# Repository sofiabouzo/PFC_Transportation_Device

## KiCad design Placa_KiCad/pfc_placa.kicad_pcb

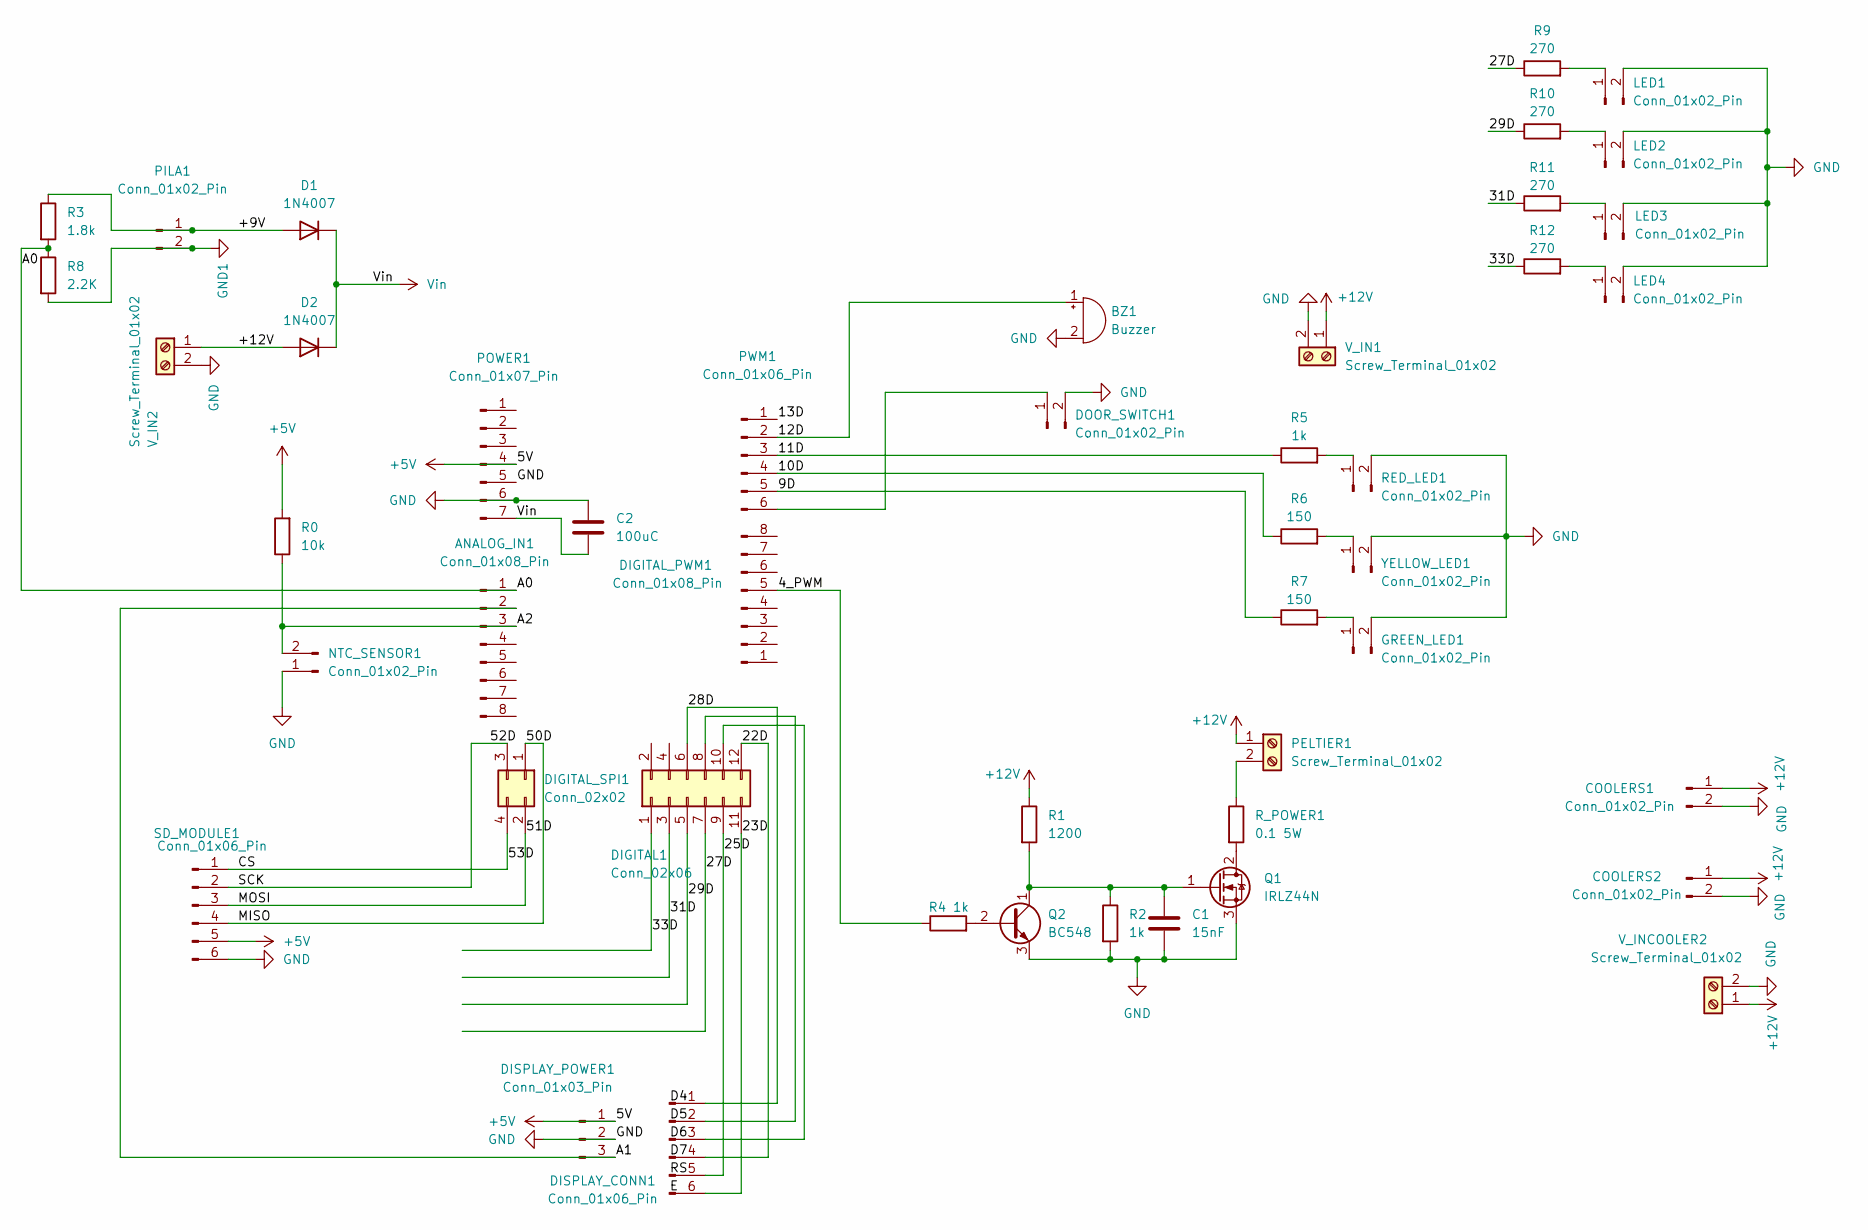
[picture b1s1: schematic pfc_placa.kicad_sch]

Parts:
ANALOG_IN1: Conn_01x08_Pin; PinHeader_1x08_P2.54mm_Vertical
BZ1: Buzzer; Buzzer_12x9.5RM7.6
C1: 15nF; C_Rect_L7.0mm_W2.5mm_P5.00mm
C2: 100uC; C_Radial_D5.0mm_H11.0mm_P2.00mm
COOLERS1, COOLERS2: Conn_01x02_Pin; JST_XH_B2B-XH-A_1x02_P2.50mm_Vertical
D1, D2: 1N4007; D_DO-41_SOD81_P10.16mm_Horizontal
DIGITAL1: Conn_02x06; PinHeader_2x06_P2.54mm_Vertical
DIGITAL_PWM1: Conn_01x08_Pin; PinHeader_1x08_P2.54mm_Vertical
DIGITAL_SPI1: Conn_02x02; PinHeader_2x02_P2.54mm_Vertical
DISPLAY_CONN1: Conn_01x06_Pin; PinHeader_1x06_P2.54mm_Vertical
DISPLAY_POWER1: Conn_01x03_Pin; PinHeader_1x03_P2.54mm_Vertical
DOOR_SWITCH1: Conn_01x02_Pin; PinHeader_1x02_P2.54mm_Vertical
GREEN_LED1: Conn_01x02_Pin; PinHeader_1x02_P2.54mm_Vertical
LED1, LED2, LED3, LED4: Conn_01x02_Pin; PinHeader_1x02_P2.54mm_Vertical
NTC_SENSOR1: Conn_01x02_Pin; JST_XH_B2B-XH-A_1x02_P2.50mm_Vertical
PELTIER1: Screw_Terminal_01x02; TerminalBlock_bornier-2_P5.08mm
PILA1: Conn_01x02_Pin; PinHeader_1x02_P2.54mm_Vertical
POWER1: Conn_01x07_Pin; PinHeader_1x07_P2.54mm_Vertical
PWM1: Conn_01x06_Pin; PinHeader_1x06_P2.54mm_Vertical
Q1: IRLZ44N; TO-220-3_Vertical
Q2: BC548; TO-92_Inline
R0: 10k; R_Axial_DIN0207_L6.3mm_D2.5mm_P7.62mm_Horizontal
R1: 1200; R_Axial_DIN0207_L6.3mm_D2.5mm_P7.62mm_Horizontal
R2, R4, R5: 1k; R_Axial_DIN0207_L6.3mm_D2.5mm_P7.62mm_Horizontal
R3: 1.8k; R_Axial_DIN0207_L6.3mm_D2.5mm_P7.62mm_Horizontal
R6, R7: 150; R_Axial_DIN0207_L6.3mm_D2.5mm_P7.62mm_Horizontal
R8: 2.2K; R_Axial_DIN0207_L6.3mm_D2.5mm_P7.62mm_Horizontal
R9, R10, R11, R12: 270; R_Axial_DIN0207_L6.3mm_D2.5mm_P7.62mm_Horizontal
RED_LED1: Conn_01x02_Pin; PinHeader_1x02_P2.54mm_Vertical
R_POWER1: 0.1 5W; R_Axial_Power_L25.0mm_W9.0mm_P27.94mm
SD_MODULE1: Conn_01x06_Pin; PinHeader_1x06_P2.54mm_Vertical
V_IN1, V_IN2: Screw_Terminal_01x02; TerminalBlock_bornier-2_P5.08mm
V_INCOOLER2: Screw_Terminal_01x02; TerminalBlock_bornier-2_P5.08mm
YELLOW_LED1: Conn_01x02_Pin; PinHeader_1x02_P2.54mm_Vertical

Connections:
+5V: DISPLAY_POWER1.1, POWER1.4, R0.2, SD_MODULE1.5
+12V: COOLERS1.1, COOLERS2.1, D2.2 (A), PELTIER1.1, R1.1, V_IN1.1, V_IN2.1, V_INCOOLER2.1
/4_PWM: DIGITAL_PWM1.5 (Pin_4), R4.1
/9D: PWM1.5, R7.1
/10D: PWM1.4, R6.1
/11D: PWM1.3, R5.1
/12D: BZ1.1 (+), PWM1.2
/13D: PWM1.1
/22D: DIGITAL1.12, DISPLAY_CONN1.4
/23D: DIGITAL1.11, DISPLAY_CONN1.6
/25D: DIGITAL1.9, DISPLAY_CONN1.5
/27D: DIGITAL1.7, R9.1
/28D: DIGITAL1.6, DISPLAY_CONN1.1
/29D: DIGITAL1.5, R10.1
/31D: DIGITAL1.3, R11.1
/33D: DIGITAL1.1, R12.1
/50D: DIGITAL_SPI1.1, SD_MODULE1.4
/51D: DIGITAL_SPI1.2, SD_MODULE1.3
/52D: DIGITAL_SPI1.3, SD_MODULE1.2
/53D: DIGITAL_SPI1.4, SD_MODULE1.1
/+9V: D1.2 (A), PILA1.1, R3.1
/A0: ANALOG_IN1.1, R3.2, R8.1
/A1: ANALOG_IN1.2, DISPLAY_POWER1.3
/A2: ANALOG_IN1.3, NTC_SENSOR1.2, R0.1
GND: BZ1.2 (-), C1.2, C2.1, COOLERS1.2, COOLERS2.2, DISPLAY_POWER1.2, DOOR_SWITCH1.2, GREEN_LED1.2, LED1.2, LED2.2, LED3.2, LED4.2, NTC_SENSOR1.1, POWER1.5, POWER1.6, Q1.3 (S), Q2.3 (E), R2.2, RED_LED1.2, SD_MODULE1.6, V_IN1.2, V_IN2.2, V_INCOOLER2.2, YELLOW_LED1.2
GND1: PILA1.2, R8.2
unnamed: DIGITAL1.8, DISPLAY_CONN1.2
unnamed: DIGITAL1.10, DISPLAY_CONN1.3
unnamed: DOOR_SWITCH1.1, PWM1.6
unnamed: GREEN_LED1.1, R7.2
unnamed: LED1.1, R9.2
unnamed: LED2.1, R10.2
unnamed: LED3.1, R11.2
unnamed: LED4.1, R12.2
unnamed: PELTIER1.2, R_POWER1.1
unnamed: Q1.2 (D), R_POWER1.2
unnamed: C1.1, Q1.1 (G), Q2.1 (C), R1.2, R2.1
unnamed: Q2.2 (B), R4.2
unnamed: R5.2, RED_LED1.1
unnamed: R6.2, YELLOW_LED1.1
Vin: C2.2, D1.1 (K), D2.1 (K), POWER1.7

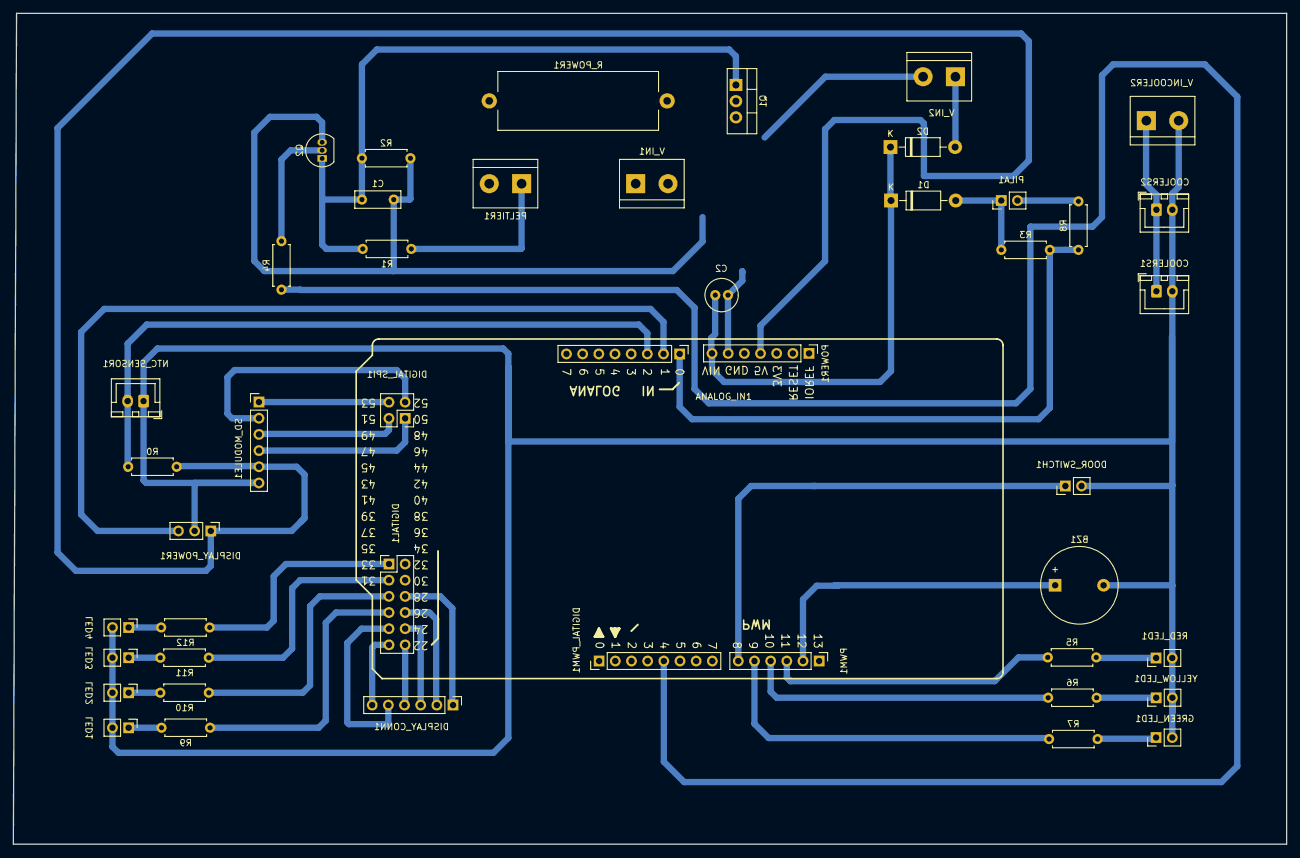
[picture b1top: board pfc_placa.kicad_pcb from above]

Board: 2 copper layers, 200.0 x 130.5 mm, 46 parts (0 on the bottom side), 40 nets.

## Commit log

2025-01-04 app created
2025-02-18 updated app & created temp db
2025-02-18 last test registered
2025-02-18 removed unnecessary files
2025-02-18 Removed .DS_Store from repository
2025-02-20 MATLAB code for PID created
2025-02-20 test 20.02 and matlab
2025-02-25 calibrated the NTC and tunned the PID controller
2025-02-25 Open source code for PID driver
2025-03-05 Matlab advances with PID
2025-03-05 some trials with the new calibration
2025-03-06 new tests with new module
2025-03-12 updated file name in arduino code
2025-03-13 New data
2025-03-18 new data with the bag inside
2025-03-20 new data: with room temperature
2025-03-25 progress with arduino display
2025-03-25 Tests
2025-03-27 minor fixes arduino
2025-03-27 new measures with BM at room temperature
2025-03-27 buzzer arduino
2025-04-01 added buzzer to the main code
2025-04-03 new measures
2025-05-08 PID control in the main code
2025-05-30 major updates
2025-07-11 updated general code
2025-07-14 app updates
2025-09-25 final app design
2025-09-25 arduino final code
